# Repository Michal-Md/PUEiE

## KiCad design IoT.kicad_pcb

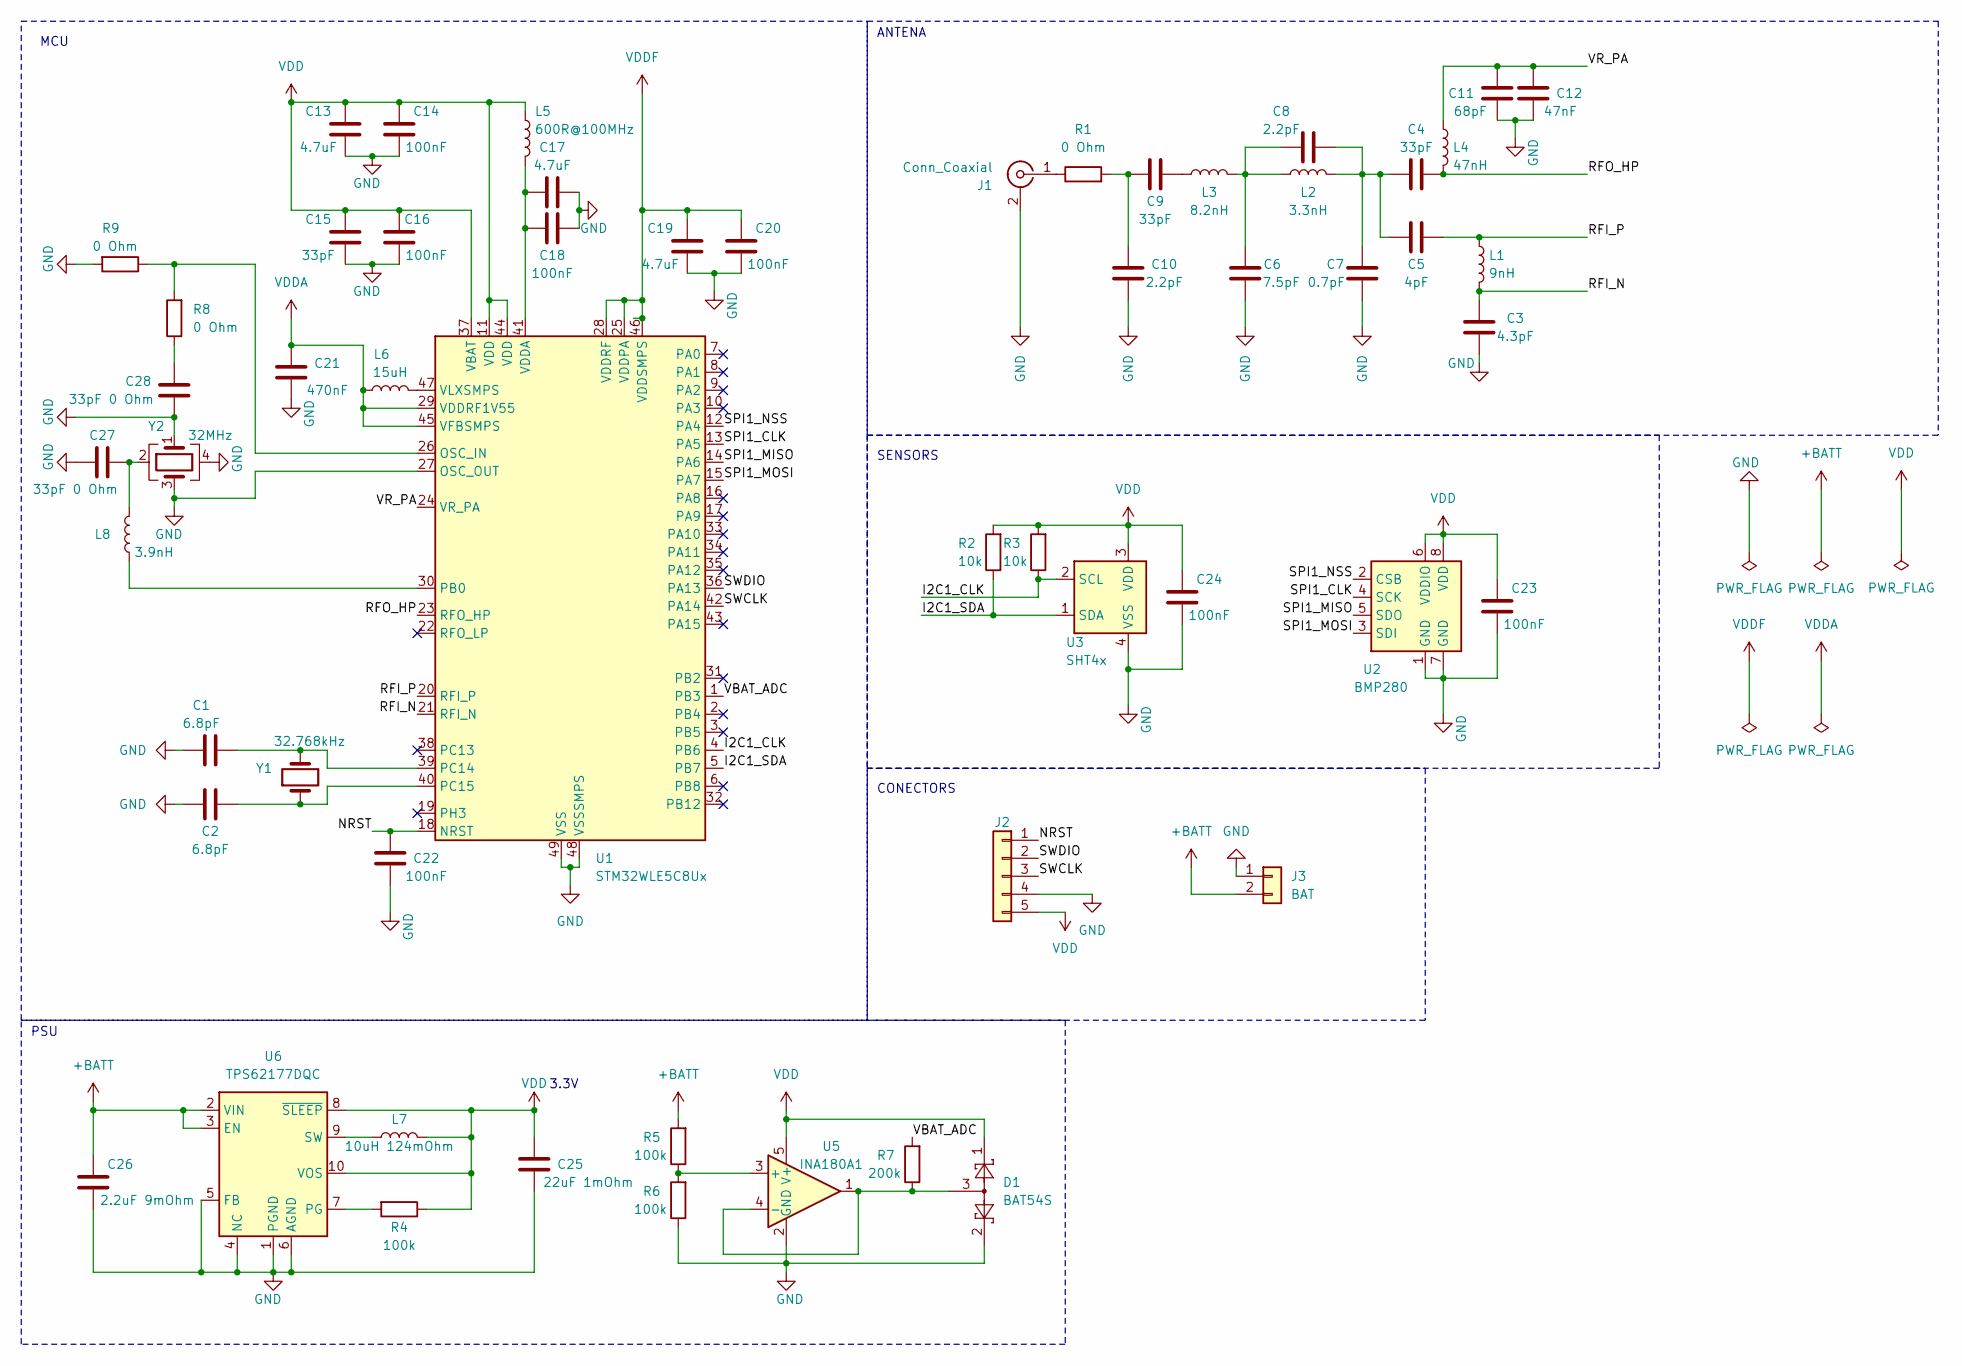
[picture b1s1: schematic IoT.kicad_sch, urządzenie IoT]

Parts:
C1, C2: 6.8pF; C_0603_1608Metric_Pad1.08x0.95mm_HandSolder
C3: 4.3pF; C_0603_1608Metric_Pad1.08x0.95mm_HandSolder
C4, C9, C15: 33pF; C_0603_1608Metric_Pad1.08x0.95mm_HandSolder
C5: 4pF; C_0603_1608Metric_Pad1.08x0.95mm_HandSolder
C6: 7.5pF; C_0603_1608Metric_Pad1.08x0.95mm_HandSolder
C7: 0.7pF; C_0603_1608Metric_Pad1.08x0.95mm_HandSolder
C8, C10: 2.2pF; C_0603_1608Metric_Pad1.08x0.95mm_HandSolder
C11: 68pF; C_0603_1608Metric_Pad1.08x0.95mm_HandSolder
C12: 47nF; C_0603_1608Metric_Pad1.08x0.95mm_HandSolder
C13, C17, C19: 4.7uF; C_0603_1608Metric_Pad1.08x0.95mm_HandSolder
C14, C16, C18, C20, C22, C23, C24: 100nF; C_0603_1608Metric_Pad1.08x0.95mm_HandSolder
C21: 470nF; C_0603_1608Metric_Pad1.08x0.95mm_HandSolder
C25: 22uF 1mOhm; C_0603_1608Metric_Pad1.08x0.95mm_HandSolder
C26: 2.2uF 9mOhm; C_0603_1608Metric_Pad1.08x0.95mm_HandSolder
C27, C28: 33pF 0 Ohm; C_0603_1608Metric_Pad1.08x0.95mm_HandSolder
D1: BAT54S; SOT-23
J1: Conn_Coaxial; SMA_Samtec_SMA-J-P-X-ST-EM1_EdgeMount
J2: Conn_01x05; PinHeader_1x05_P2.54mm_Vertical
J3: BAT; TerminalBlock_TE_282834-2_1x02_P2.54mm_Horizontal
L1: 9nH; L_0402_1005Metric_Pad0.77x0.64mm_HandSolder
L2: 3.3nH; L_0402_1005Metric_Pad0.77x0.64mm_HandSolder
L3: 8.2nH; L_0805_2012Metric_Pad1.15x1.40mm_HandSolder
L4: 47nH; L_0402_1005Metric_Pad0.77x0.64mm_HandSolder
L5: 600R@100MHz; L_0603_1608Metric_Pad1.05x0.95mm_HandSolder
L6: 15uH; L_0805_2012Metric_Pad1.15x1.40mm_HandSolder
L7: 10uH 124mOhm; L_TDK_SLF6025
L8: 3.9nH; L_0402_1005Metric_Pad0.77x0.64mm_HandSolder
R1, R8, R9: 0 Ohm; R_0603_1608Metric_Pad0.98x0.95mm_HandSolder
R2, R3: 10k; R_0603_1608Metric_Pad0.98x0.95mm_HandSolder
R4, R5, R6: 100k; R_0603_1608Metric_Pad0.98x0.95mm_HandSolder
R7: 200k; R_0603_1608Metric_Pad0.98x0.95mm_HandSolder
U1: STM32WLE5C8Ux; QFN-48-1EP_7x7mm_P0.5mm_EP5.6x5.6mm
U2: BMP280; Bosch_LGA-8_2x2.5mm_P0.65mm_ClockwisePinNumbering
U3: SHT4x; Sensirion_DFN-4_1.5x1.5mm_P0.8mm_SHT4x_NoCentralPad
U5: INA180A1; SOT-23-5
U6: TPS62177DQC; WSON-10-1EP_2x3mm_P0.5mm_EP0.84x2.4mm_ThermalVias
Y1: 32.768kHz; Crystal_SMD_2012-2Pin_2.0x1.2mm_HandSoldering
Y2: 32MHz; Crystal_SMD_2016-4Pin_2.0x1.6mm

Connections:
+BATT: C26.1, J3.2, R5.2, U6.2 (VIN), U6.3 (EN)
/I2C1_CLK: R3.1, U1.4 (PB6), U3.2 (SCL)
/I2C1_SDA: R2.1, U1.5 (PB7), U3.1 (SDA)
/NRST: C22.1, J2.1, U1.18 (NRST)
/RFI_N: C3.1, L1.2, U1.21 (RFI_N)
/RFI_P: C5.1, L1.1, U1.20 (RFI_P)
/RFO_HP: C4.1, L4.2, U1.23 (RFO_HP)
/SPI1_CLK: U1.13 (PA5), U2.4 (SCK)
/SPI1_MISO: U1.14 (PA6), U2.5 (SDO)
/SPI1_MOSI: U1.15 (PA7), U2.3 (SDI)
/SPI1_NSS: U1.12 (PA4), U2.2 (CSB)
/SWCLK: J2.3, U1.42 (PA14)
/SWDIO: J2.2, U1.36 (PA13)
/VBAT_ADC: R7.2, U1.1 (PB3)
/VR_PA: C11.1, C12.1, L4.1, U1.24 (VR_PA)
GND: C1.2, C2.2, C3.2, C6.2, C7.2, C10.2, C11.2, C12.2, C13.2, C14.2, C15.2, C16.2, C17.2, C18.2, C19.2, C20.2, C21.1, C22.2, C23.2, C24.2, C25.2, C26.2, C27.1, C28.1, D1.2, J1.2 (Ext), J2.4, J3.1, R6.1, R9.2, U1.27 (OSC_OUT), U1.48 (VSSSMPS), U1.49 (VSS), U2.1 (GND), U2.7 (GND), U3.4 (VSS), U5.2 (GND), U6.1 (PGND), U6.4 (NC), U6.5 (FB), U6.6 (AGND), Y2.1, Y2.3, Y2.4
unnamed: C4.2, C5.2, C7.1, C8.1, L2.2
unnamed: C6.1, C8.2, L2.1, L3.2
unnamed: C9.1, L3.1
unnamed: C9.2, C10.1, R1.2
unnamed: C27.2, L8.2, Y2.2
unnamed: C28.2, R8.1
unnamed: J1.1 (In), R1.1
unnamed: R8.2, R9.1, U1.26 (OSC_IN)
unnamed: L8.1, U1.30 (PB0)
unnamed: C1.1, U1.39 (PC14), Y1.2
unnamed: C2.1, U1.40 (PC15), Y1.1
unnamed: C17.1, C18.1, L5.2, U1.41 (VDDA)
unnamed: L6.2, U1.47 (VLXSMPS)
unnamed: R5.1, R6.2, U5.3 (+)
unnamed: D1.3, R7.1, U5.1, U5.4 (-)
unnamed: R4.2, U6.7 (PG)
unnamed: L7.1, U6.9 (SW)
VDD: C13.1, C14.1, C15.1, C16.1, C23.1, C24.1, C25.1, D1.1, J2.5, L5.1, L7.2, R2.2, R3.2, R4.1, U1.11 (VDD), U1.37 (VBAT), U1.44 (VDD), U2.6 (VDDIO), U2.8 (VDD), U3.3 (VDD), U5.5 (V+), U6.8 (~SLEEP), U6.10 (VOS)
VDDA: C21.2, L6.1, U1.29 (VDDRF1V55), U1.45 (VFBSMPS)
VDDF: C19.1, C20.1, U1.25 (VDDPA), U1.28 (VDDRF), U1.46 (VDDSMPS)

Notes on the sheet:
3.3V
PSU
ANTENA
SENSORS
CONECTORS
MCU

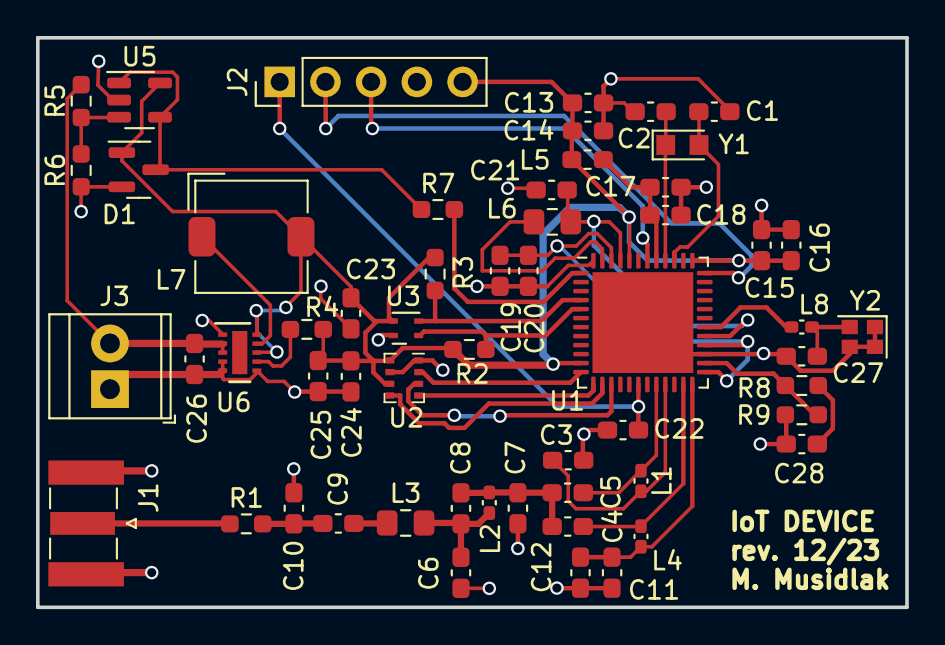
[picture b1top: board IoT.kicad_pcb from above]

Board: 2 copper layers, 48.3 x 31.6 mm, 56 parts (0 on the bottom side), 36 nets.

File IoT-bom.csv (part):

;Source:;C:\Users\micha\Desktop\PUEiE2\laby\1 â kopia\pierwszy\pierwszy.kicad_sch;;;;;;;;;;;;
;;;;;;;;;;;;;;
;Date:;26.12.2023 20:17;;;;;;;;;;;;
;;;;;;;;;;;;;;
;Component Count:;56;;;;;;;;;;;;
;;;;;;;;;;;;;;
Lp.;Ref;Lczba;Wartoæ;Nazwa;Footprint;Opis;Dostawca;Koszt j.(1 szt);Cena(1 PCB);Koszt j.(10 szt);Cena(10 PCB);Koszt j.(100 szt);Cena(100 PCB);link
1;C1, C2;2;6.8pF;C;Capacitor_SMD:C_0603_1608Metric_Pad1.08x0.95mm_HandSolder;Unpolarized capacitor;tme.eu;0,37;0,74;0,256;0,512;0,1251;0,2502;https://www.tme.eu/pl/details/06031a6r8cat2a/kondensatory-ml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
2;C3;1;4.3pF;C;Capacitor_SMD:C_0603_1608Metric_Pad1.08x0.95mm_HandSolder;Unpolarized capacitor;mouser.pl;0,43;0,43;0,088;0,088;0,051;0,051;https://www.mouser.pl/ProductDetail/KEMET/C0603C439D1HACTU?q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
3;C4, C9, C15;3;33pF;C;Capacitor_SMD:C_0603_1608Metric_Pad1.08x0.95mm_HandSolder;Unpolarized capacitor;mouser.pl;0,602;1,806;0,477;1,431;0,241;0,723;https://www.mouser.pl/ProductDetail/KYOCERA-AVX/KGM15ACG1H33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
4;C5;1;4pF;C;Capacitor_SMD:C_0603_1608Metric_Pad1.08x0.95mm_HandSolder;Unpolarized capacitor;mouser.pl;0,431;0,431;0,31;0,31;0,148;0,148;https://www.mouser.pl/ProductDetail/TDK/C1608C0G1H040C080AA?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
5;C6;1;7.5pF;C;Capacitor_SMD:C_0603_1608Metric_Pad1.08x0.95mm_HandSolder;Unpolarized capacitor;mouser.pl;0,431;0,431;0,25;0,25;0,111;0,111;https://www.mouser.pl/ProductDetail/KYOCERA-AVX/06035A7R5CAT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
6;C7;1;0.7pF;C;Capacitor_SMD:C_0603_1608Metric_Pad1.08x0.95mm_HandSolder;Unpolarized capacitor;mouser.pl;0,431;0,431;0,181;0,181;0,106;0,106;https://www.mouser.pl/ProductDetail/YAGEO/CC0603BRNPO9BNR70?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
7;C8, C10;2;2.2pF;C;Capacitor_SMD:C_0603_1608Metric_Pad1.08x0.95mm_HandSolder;Unpolarized capacitor;mouser.pl;0,431;0,862;0,232;0,464;0,12;0,24;https://www.mouser.pl/ProductDetail/Vishay-Vitramon/VJ0603A2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
8;C11;1;68pF;C;Capacitor_SMD:C_0603_1608Metric_Pad1.08x0.95mm_HandSolder;Unpolarized capacitor;mouser.pl;0,431;0,431;0,162;0,162;0,079;0,079;https://www.mouser.pl/ProductDetail/KEMET/C0603C680M5HACTU?q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
9;C12;1;47nF;C;Capacitor_SMD:C_0603_1608Metric_Pad1.08x0.95mm_HandSolder;Unpolarized capacitor;mouser.pl;0,431;0,431;0,269;0,269;0,116;0,116;https://www.mouser.pl/ProductDetail/KYOCERA-AVX/KAM15AR71H47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
10;C13, C17, C19;3;4.7uF;C;Capacitor_SMD:C_0603_1608Metric_Pad1.08x0.95mm_HandSolder;Unpolarized capacitor;mouser.pl;0,431;1,293;0,204;0,612;0,116;0,348;https://www.mouser.pl/ProductDetail/TAIYO-YUDEN/JMK107C6475M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
11;C14, C16, C18, C20, C22, C23, C24;7;100nF;C;Capacitor_SMD:C_0603_1608Metric_Pad1.08x0.95mm_HandSolder;Unpolarized capacitor;mouser.pl;0,431;3,017;0,157;1,099;0,093;0,651;https://www.mouser.pl/ProductDetail/KYOCERA-AVX/KAM15AR71H10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
12;C21;1;470nF;C;Capacitor_SMD:C_0603_1608Metric_Pad1.08x0.95mm_HandSolder;Unpolarized capacitor;mouser.pl;0,431;0,431;0,218;0,218;0,111;0,111;https://www.mouser.pl/ProductDetail/TAIYO-YUDEN/TMK107BJ474K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
13;C25;1;22uF 1mOhm;C;Capacitor_SMD:C_0603_1608Metric_Pad1.08x0.95mm_HandSolder;Unpolarized capacitor;mouser.pl;0,861;0,861;0,338;0,338;0,194;0,194;https://www.mouser.pl/ProductDetail/Murata-Electronics/GRM18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
14;C26;1;2.2uF 9mOhm;C;Capacitor_SMD:C_0603_1608Metric_Pad1.08x0.95mm_HandSolder;Unpolarized capacitor;mouser.pl;0,773;0,773;0,287;0,287;0,167;0,167;https://www.mouser.pl/ProductDetail/Murata-Electronics/GRM18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
15;C27, C28;2;33pF 0 Ohm;C;Capacitor_SMD:C_0603_1608Metric_Pad1.08x0.95mm_HandSolder;Unpolarized capacitor;mouser.pl;0,648;1,296;0,458;0,916;0,218;0,436;https://www.mouser.pl/ProductDetail/Murata-Electronics/GRM18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
16;D1;1;BAT54S;BAT54A;Package_TO_SOT_SMD:SOT-23;schottky barrier diode;mouser.pl;0,82;0,82;0,523;0,523;0,315;0,315;https://www.mouser.pl/ProductDetail/Nexperia/BAT54A215?qs=me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
17;J1;1;Conn_Coaxial;Conn_Coaxial;Connector_Coaxial:SMA_Samtec_SMA-J-P-X-ST-EM1_EdgeMount;coaxial connector (BNC, SMA, SMB, SMC, Cinch/RCA, LEMO, ...);tme.eu;11,51;11,51;8,23;8,23;5,9;5,9;https://www.tme.eu/pl/details/rf2143t1750g/zlacza-sma-smb-sm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
18;J2;1;Conn_01x05;Conn_01x05;Connector_PinHeader_2.54mm:PinHeader_1x05_P2.54mm_Vertical;Generic connector, single row, 01x05, script generated (kicad-library-utils/schlib/autogen/connector/);mouser.pl;0,56;0,56;0,287;0,287;0,278;0,278;https://www.mouser.pl/ProductDetail/Amphenol-Commercial-Prod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
19;J3;1;BAT;Conn_01x02;TerminalBlock_TE-Connectivity:TerminalBlock_TE_282834-2_1x02_P2.54mm_Horizontal;Generic connector, single row, 01x02, script generated (kicad-library-utils/schlib/autogen/connector/);tme.eu;2,375;2,375;2,375;2,375;1,341;1,341;https://www.tme.eu/pl/details/dg308-2.54-02p/listwy-zaciskow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
20;L1;1;9nH;L;Inductor_SMD:L_0402_1005Metric_Pad0.77x0.64mm_HandSolder;Inductor;mouser.pl;0,602;0,602;0,421;0,421;0,333;0,333;https://www.mouser.pl/ProductDetail/Murata-Electronics/LQW15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
21;L2;1;3.3nH;L;Inductor_SMD:L_0402_1005Metric_Pad0.77x0.64mm_HandSolder;Inductor;mouser.pl;0,69;0,69;0,463;0,463;0,357;0,357;https://www.mouser.pl/ProductDetail/Murata-Electronics/LQW15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
22;L3;1;8.2nH;L;Inductor_SMD:L_0805_2012Metric_Pad1.15x1.40mm_HandSolder;Inductor;mouser.pl;0,602;0,602;0,542;0,542;0,412;0,412;https://www.mouser.pl/ProductDetail/Murata-Electronics/LQW2B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
23;L4;1;47nH;L;Inductor_SMD:L_0402_1005Metric_Pad0.77x0.64mm_HandSolder;Inductor;mouser.pl;0,602;0,602;0,394;0,394;0,31;0,31;https://www.mouser.pl/ProductDetail/Murata-Electronics/LQW15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
24;L5;1;600R@100MHz;L;Inductor_SMD:L_0603_1608Metric_Pad1.05x0.95mm_HandSolder;Inductor;digikey.pl;0,4;0,4;0,099;0,099;0,0888;0,0888;https://www.digikey.pl/en/products/detail/tai-tech-advanced-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
25;L6;1;15uH;L;Inductor_SMD:L_0805_2012Metric_Pad1.15x1.40mm_HandSolder;Inductor;mouser.pl;0,519;0,519;0,338;0,338;0,264;0,264;https://www.mouser.pl/ProductDetail/TDK/MLZ2012M150WT000?qs=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
26;L7;1;10uH 124mOhm;L;Inductor_SMD:L_TDK_SLF6025;Inductor;mouser.pl;3,49;3,49;2,52;2,52;1,81;1,81;https://www.mouser.pl/ProductDetail/Sumida/CDRH5D18NP-100NC?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
27;L8;1;3.9nH;L;Inductor_SMD:L_0402_1005Metric_Pad0.77x0.64mm_HandSolder;Inductor;mouser.pl;0,648;0,648;0,431;0,431;0,338;0,338;https://www.mouser.pl/ProductDetail/Murata-Electronics/LQW15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
28;R1, R8, R9;3;0 Ohm;R;Resistor_SMD:R_0603_1608Metric_Pad0.98x0.95mm_HandSolder;Resistor;mouser.pl;0,431;1,293;0,06;0,18;0,032;0,096;https://www.mouser.pl/ProductDetail/Vishay-Dale/CRCW06030000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
29;R2, R3;2;10k;R;Resistor_SMD:R_0603_1608Metric_Pad0.98x0.95mm_HandSolder;Resistor;mouser.pl;0,431;0,862;0,083;0,166;0,037;0,074;https://www.mouser.pl/ProductDetail/Vishay-Dale/CRCW060310K0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
30;R4, R5, R6;3;100k;R;Resistor_SMD:R_0603_1608Metric_Pad0.98x0.95mm_HandSolder;Resistor;mouser.pl;0,431;1,293;0,083;0,249;0,037;0,111;https://www.mouser.pl/ProductDetail/Vishay-Dale/CRCW0603100K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
31;R7;1;200k;R;Resistor_SMD:R_0603_1608Metric_Pad0.98x0.95mm_HandSolder;Resistor;mouser.pl;0,431;0,431;0,218;0,218;0,093;0,093;https://www.mouser.pl/ProductDetail/ROHM-Semiconductor/SDR03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
32;U1;1;STM32WLE5C8Ux;STM32WLE5C8Ux;Package_DFN_QFN:QFN-48-1EP_7x7mm_P0.5mm_EP5.6x5.6mm;STMicroelectronics Arm Cortex-M4 MCU, 64KB flash, 20KB RAM, 48 MHz, 1.8-3.6V, 29 GPIO, UFQFPN48;mouser.pl;25,88;25,88;23,8;23,8;20,88;20,88;https://www.mouser.pl/ProductDetail/STMicroelectronics/STM32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
33;U2;1;BMP280;BMP280;Package_LGA:Bosch_LGA-8_2x2.5mm_P0.65mm_ClockwisePinNumbering;Absolute Barometric Pressure Sensor, LGA-8;mouser.pl;27,32;27,32;17,55;17,55;16,99;16,99;https://www.mouser.pl/ProductDetail/Bosch-Sensortec/BME280?q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
34;U3;1;SHT4x;SHT4x;Sensor_Humidity:Sensirion_DFN-4_1.5x1.5mm_P0.8mm_SHT4x_NoCentralPad;Digital Humidity and Temperature Sensor, +/-1%RH, +/-0.1degC, I2C, 1.08-3.6V, 16bit, DFN-4;mouser.pl;11,71;11,71;7,22;7,22;6,9;6,9;https://www.mouser.pl/ProductDetail/Sensirion/SHT40-AD1B-R2?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
35;U5;1;INA180A1;INA180A1;Package_TO_SOT_SMD:SOT-23-5;Current Sense Amplifier, 1 Circuit, Rail-to-Rail, 26V, Gain 20 V/V, SOT-23-5;mouser.pl;2,5;2,5;2,12;2,12;1,58;1,58;https://www.mouser.pl/ProductDetail/Texas-Instruments/INA180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
